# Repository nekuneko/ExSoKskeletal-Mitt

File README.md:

# ExSoKskeletal Mitt
Robotic Hand for ICTUS patients based on SoK (System on Keyring) boards.

Usign Autodesk EAGLE 9.5.2

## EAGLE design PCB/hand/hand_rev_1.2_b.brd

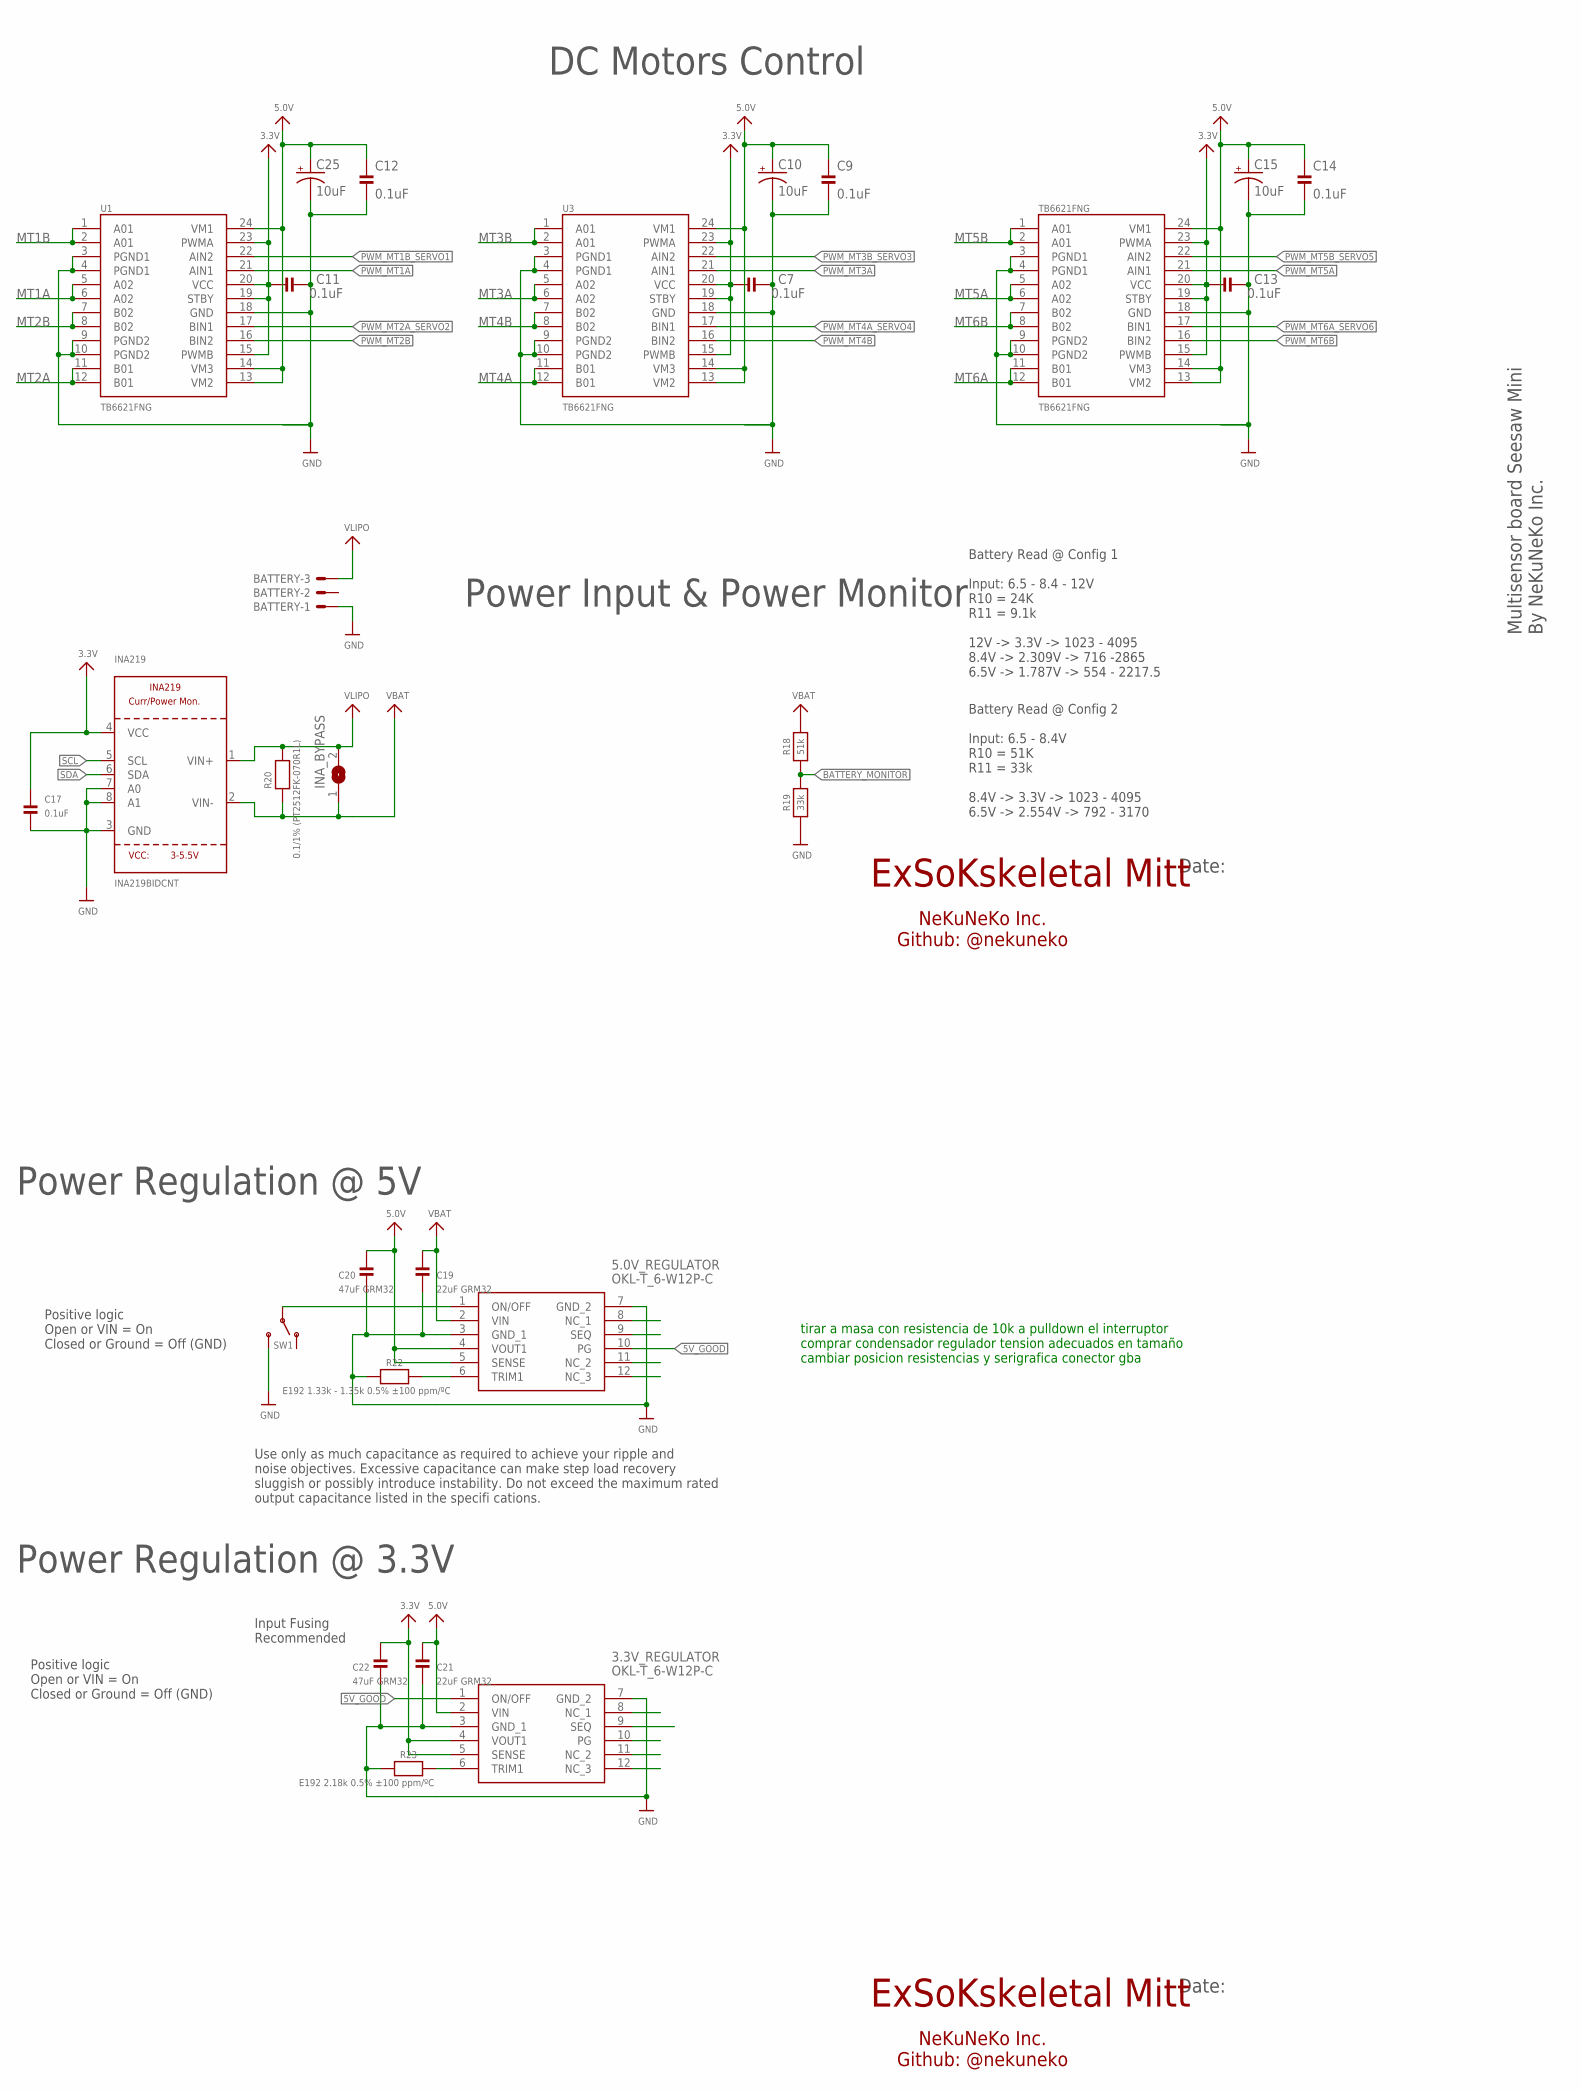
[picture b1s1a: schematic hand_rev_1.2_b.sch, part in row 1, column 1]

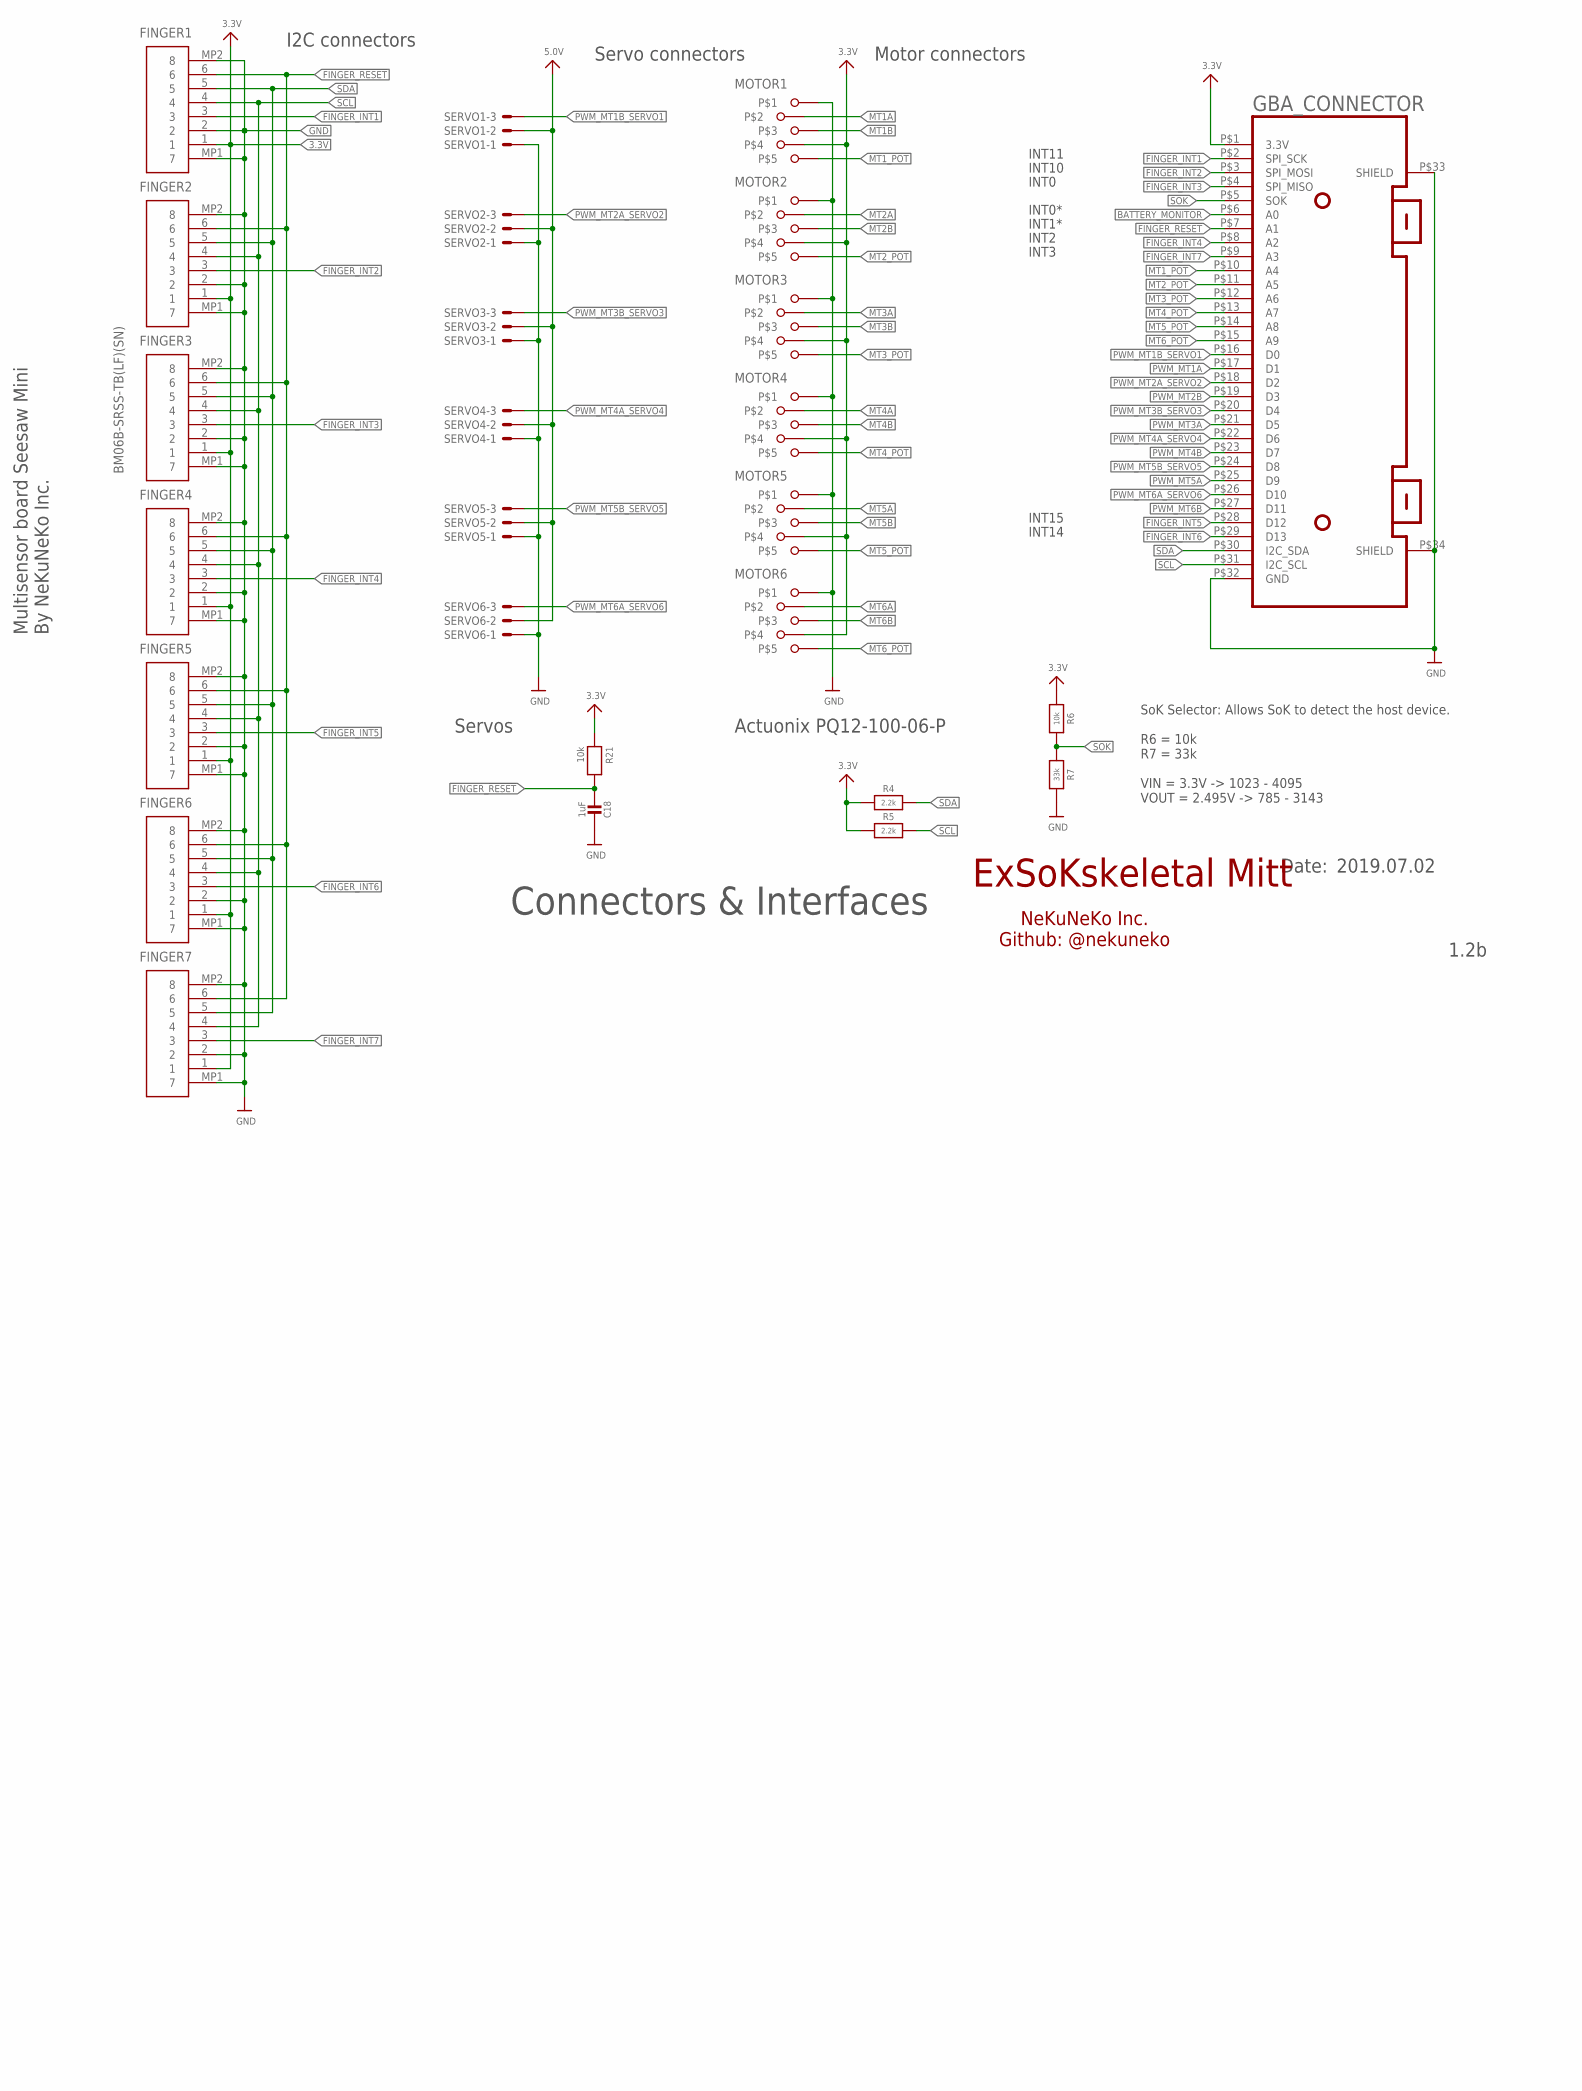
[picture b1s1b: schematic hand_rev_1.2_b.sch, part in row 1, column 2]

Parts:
3.3V_REGULATOR, 5.0V_REGULATOR: OKL-T_6-W12P-C; OKL-T3-W12
BATTERY: JST-XH-03-PIN-LONG-PAD; JST-XH-03-PACKAGE-LONG-PAD
C7, C9, C11, C12, C13, C14, C17: 0.1uF; _0603
C10, C15, C25: 10uF; 0603-POLAR; MPN F981A106MMA
C18: 1uF; MICROBUILDER__0603
C19, C21: 22uF GRM32; 1206
C20, C22: 47uF GRM32; 1206
FINGER1, FINGER2, FINGER3, FINGER4, FINGER5, FINGER6, FINGER7: BM06B-SRSS-TB(LF)(SN); BM06BSRSSTBLFSN
GBA_CONNECTOR: GBA_CARTRIDGEGBA_CARTRIDGE2; GBA_CARTRIDGE2
INA219: INA219BIDCNT; SOT23-8
INA_BYPASS: SOLDERJUMPERREFLOW_NOPASTE; SOLDERJUMPER_REFLOW_NOPASTE
MOTOR1, MOTOR2, MOTOR3, MOTOR4, MOTOR5, MOTOR6: Actuonix PQ12-100-06-P; 5PIN
R4, R5: 2.2k; _0603
R6, R21: 10k; _0603
R7, R19: 33k; _0603
R18: 51k; _0603
R20: 0.1/1% (PT2512FK-070R1L); 2512
R22: E192 1.33k - 1.35k 0.5% ±100 ppm/ºC; _0603
R23: E192 2.18k 0.5% ±100 ppm/ºC; _0603
SERVO1, SERVO2, SERVO3, SERVO4, SERVO5, SERVO6: JST-XH-03-PIN-LONG-PAD; JST-XH-03-PACKAGE-LONG-PAD
SW1: SWITCH_SPDT; SPDT_SMT_SSSS811101
TB6621FNG: TB6621FNG; SSOP24
U1, U3: TB6621FNG; SSOP24

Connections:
3.3V: 3.3V_REGULATOR.4 (VOUT1), 3.3V_REGULATOR.5 (SENSE), C7.1, C11.1, C13.1, C17.2, C22.1, FINGER1.1, FINGER2.1, FINGER3.1, FINGER4.1, FINGER5.1, FINGER6.1, FINGER7.1, GBA_CONNECTOR.P$1 (3.3V), INA219.4 (VCC), MOTOR1.4, MOTOR2.4, MOTOR3.4, MOTOR4.4, MOTOR5.4, MOTOR6.4, R4.1, R5.1, R6.1, R21.1, TB6621FNG.15 (PWMB), TB6621FNG.19 (STBY), TB6621FNG.20 (VCC), TB6621FNG.23 (PWMA), U1.15 (PWMB), U1.19 (STBY), U1.20 (VCC), U1.23 (PWMA), U3.15 (PWMB), U3.19 (STBY), U3.20 (VCC), U3.23 (PWMA)
5.0V: 3.3V_REGULATOR.2 (VIN), 5.0V_REGULATOR.4 (VOUT1), 5.0V_REGULATOR.5 (SENSE), C9.2, C10.+, C12.2, C14.2, C15.+, C20.1, C21.1, C25.+, SERVO1.2, SERVO2.2, SERVO3.2, SERVO4.2, SERVO5.2, SERVO6.2, TB6621FNG.13 (VM2), TB6621FNG.14 (VM3), TB6621FNG.24 (VM1), U1.13 (VM2), U1.14 (VM3), U1.24 (VM1), U3.13 (VM2), U3.14 (VM3), U3.24 (VM1)
5V_GOOD: 3.3V_REGULATOR.1 (ON/OFF), 5.0V_REGULATOR.10 (PG)
BATTERY_MONITOR: GBA_CONNECTOR.P$6 (A0), R18.1, R19.2
FINGER_!RESET: C18.2, FINGER1.6, FINGER2.6, FINGER3.6, FINGER4.6, FINGER5.6, FINGER6.6, FINGER7.6, GBA_CONNECTOR.P$7 (A1), R21.2
FINGER_INT1: FINGER1.3, GBA_CONNECTOR.P$2 (SPI_SCK)
FINGER_INT2: FINGER2.3, GBA_CONNECTOR.P$3 (SPI_MOSI)
FINGER_INT3: FINGER3.3, GBA_CONNECTOR.P$4 (SPI_MISO)
FINGER_INT4: FINGER4.3, GBA_CONNECTOR.P$8 (A2)
FINGER_INT5: FINGER5.3, GBA_CONNECTOR.P$28 (D12)
FINGER_INT6: FINGER6.3, GBA_CONNECTOR.P$29 (D13)
FINGER_INT7: FINGER7.3, GBA_CONNECTOR.P$9 (A3)
GND: 3.3V_REGULATOR.3 (GND_1), 3.3V_REGULATOR.7 (GND_2), 5.0V_REGULATOR.3 (GND_1), 5.0V_REGULATOR.7 (GND_2), BATTERY.1, C7.2, C9.1, C10.-, C11.2, C12.1, C13.2, C14.1, C15.-, C17.1, C18.1, C19.2, C20.2, C21.2, C22.2, C25.-, FINGER1.2, FINGER1.MP1 (7), FINGER1.MP2 (8), FINGER2.2, FINGER2.MP1 (7), FINGER2.MP2 (8), FINGER3.2, FINGER3.MP1 (7), FINGER3.MP2 (8), FINGER4.2, FINGER4.MP1 (7), FINGER4.MP2 (8), FINGER5.2, FINGER5.MP1 (7), FINGER5.MP2 (8), FINGER6.2, FINGER6.MP1 (7), FINGER6.MP2 (8), FINGER7.2, FINGER7.MP1 (7), FINGER7.MP2 (8), GBA_CONNECTOR.P$32 (GND), GBA_CONNECTOR.P$33 (SHIELD), GBA_CONNECTOR.P$34 (SHIELD), INA219.3 (GND), INA219.7 (A0), INA219.8 (A1), MOTOR1.1, MOTOR2.1, MOTOR3.1, MOTOR4.1, MOTOR5.1, MOTOR6.1, R7.2, R19.1, R22.2, R23.2, SERVO1.1, SERVO2.1, SERVO3.1, SERVO4.1, SERVO5.1, SERVO6.1, SW1.C (S), TB6621FNG.3 (PGND1), TB6621FNG.4 (PGND1), TB6621FNG.9 (PGND2), TB6621FNG.10 (PGND2), TB6621FNG.18 (GND), U1.3 (PGND1), U1.4 (PGND1), U1.9 (PGND2), U1.10 (PGND2), U1.18 (GND), U3.3 (PGND1), U3.4 (PGND1), U3.9 (PGND2), U3.10 (PGND2), U3.18 (GND)
MT1A: MOTOR1.2, U1.5 (A02), U1.6 (A02)
MT1B: MOTOR1.3, U1.1 (A01), U1.2 (A01)
MT1_POT: GBA_CONNECTOR.P$10 (A4), MOTOR1.5
MT2A: MOTOR2.2, U1.11 (B01), U1.12 (B01)
MT2B: MOTOR2.3, U1.7 (B02), U1.8 (B02)
MT2_POT: GBA_CONNECTOR.P$11 (A5), MOTOR2.5
MT3A: MOTOR3.2, U3.5 (A02), U3.6 (A02)
MT3B: MOTOR3.3, U3.1 (A01), U3.2 (A01)
MT3_POT: GBA_CONNECTOR.P$12 (A6), MOTOR3.5
MT4A: MOTOR4.2, U3.11 (B01), U3.12 (B01)
MT4B: MOTOR4.3, U3.7 (B02), U3.8 (B02)
MT4_POT: GBA_CONNECTOR.P$13 (A7), MOTOR4.5
MT5A: MOTOR5.2, TB6621FNG.5 (A02), TB6621FNG.6 (A02)
MT5B: MOTOR5.3, TB6621FNG.1 (A01), TB6621FNG.2 (A01)
MT5_POT: GBA_CONNECTOR.P$14 (A8), MOTOR5.5
MT6A: MOTOR6.2, TB6621FNG.11 (B01), TB6621FNG.12 (B01)
MT6B: MOTOR6.3, TB6621FNG.7 (B02), TB6621FNG.8 (B02)
MT6_POT: GBA_CONNECTOR.P$15 (A9), MOTOR6.5
unnamed: 5.0V_REGULATOR.6 (TRIM1), R22.1
unnamed: 3.3V_REGULATOR.6 (TRIM1), R23.1
PWM_MT1A: GBA_CONNECTOR.P$17 (D1), U1.21 (AIN1)
PWM_MT1B_SERVO1: GBA_CONNECTOR.P$16 (D0), SERVO1.3, U1.22 (AIN2)
PWM_MT2A_SERVO2: GBA_CONNECTOR.P$18 (D2), SERVO2.3, U1.17 (BIN1)
PWM_MT2B: GBA_CONNECTOR.P$19 (D3), U1.16 (BIN2)
PWM_MT3A: GBA_CONNECTOR.P$21 (D5), U3.21 (AIN1)
PWM_MT3B_SERVO3: GBA_CONNECTOR.P$20 (D4), SERVO3.3, U3.22 (AIN2)
PWM_MT4A_SERVO4: GBA_CONNECTOR.P$22 (D6), SERVO4.3, U3.17 (BIN1)
PWM_MT4B: GBA_CONNECTOR.P$23 (D7), U3.16 (BIN2)
PWM_MT5A: GBA_CONNECTOR.P$25 (D9), TB6621FNG.21 (AIN1)
PWM_MT5B_SERVO5: GBA_CONNECTOR.P$24 (D8), SERVO5.3, TB6621FNG.22 (AIN2)
PWM_MT6A_SERVO6: GBA_CONNECTOR.P$26 (D10), SERVO6.3, TB6621FNG.17 (BIN1)
PWM_MT6B: GBA_CONNECTOR.P$27 (D11), TB6621FNG.16 (BIN2)
REG_5V_ON: 5.0V_REGULATOR.1 (ON/OFF), SW1.B
SCL: FINGER1.4, FINGER2.4, FINGER3.4, FINGER4.4, FINGER5.4, FINGER6.4, FINGER7.4, GBA_CONNECTOR.P$31 (I2C_SCL), INA219.5 (SCL), R5.2
SDA: FINGER1.5, FINGER2.5, FINGER3.5, FINGER4.5, FINGER5.5, FINGER6.5, FINGER7.5, GBA_CONNECTOR.P$30 (I2C_SDA), INA219.6 (SDA), R4.2
SOK: GBA_CONNECTOR.P$5 (SOK), R6.2, R7.1
VBAT: 5.0V_REGULATOR.2 (VIN), C19.1, INA219.2 (VIN-), INA_BYPASS.1, R18.2, R20.1
VLIPO: BATTERY.3, INA219.1 (VIN+), INA_BYPASS.2, R20.2

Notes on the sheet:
ExSoKskeletal Mitt
INT11
INT10
INT0
INT0*
INT1*
INT2
INT3
INT14
INT15
Battery Read @ Config 2 Input: 6.5 - 8.4V R10 = 51K R11 = 33k 8.4V -> 3.3V -> 1023 - 4095 6.5V -> 2.554V -> 792 - 3170
Power Input & Power Monitor
Power Regulation @ 5V
Power Regulation @ 3.3V
DC Motors Control
Connectors & Interfaces
NeKuNeKo Inc. Github: @nekuneko
Date:
SoK Selector: Allows SoK to detect the host device. R6 = 10k R7 = 33k VIN = 3.3V -> 1023 - 4095 VOUT = 2.495V -> 785 - 3143
I2C connectors
Servo connectors
Motor connectors
Actuonix PQ12-100-06-P
Multisensor board Seesaw Mini By NeKuNeKo Inc.
Servos
Battery Read @ Config 1 Input: 6.5 - 8.4 - 12V R10 = 24K R11 = 9.1k 12V -> 3.3V -> 1023 - 4095 8.4V -> 2.309V -> 716 -2865 6.5V -> 1.787V -> 554 - 2217.5
Input Fusing Recommended
Positive logic Open or VIN = On Closed or Ground = Off (GND)
Use only as much capacitance as required to achieve your ripple and noise objectives. Excessive capacitance can make step load recovery sluggish or possibly introduce instability. Do not exceed the maximum rated output capacitance listed in the specifi cations.
tirar a masa con resistencia de 10k a pulldown el interruptor comprar condensador regulador tension adecuados en tamaño cambiar posicion resistencias y serigrafica conector gba

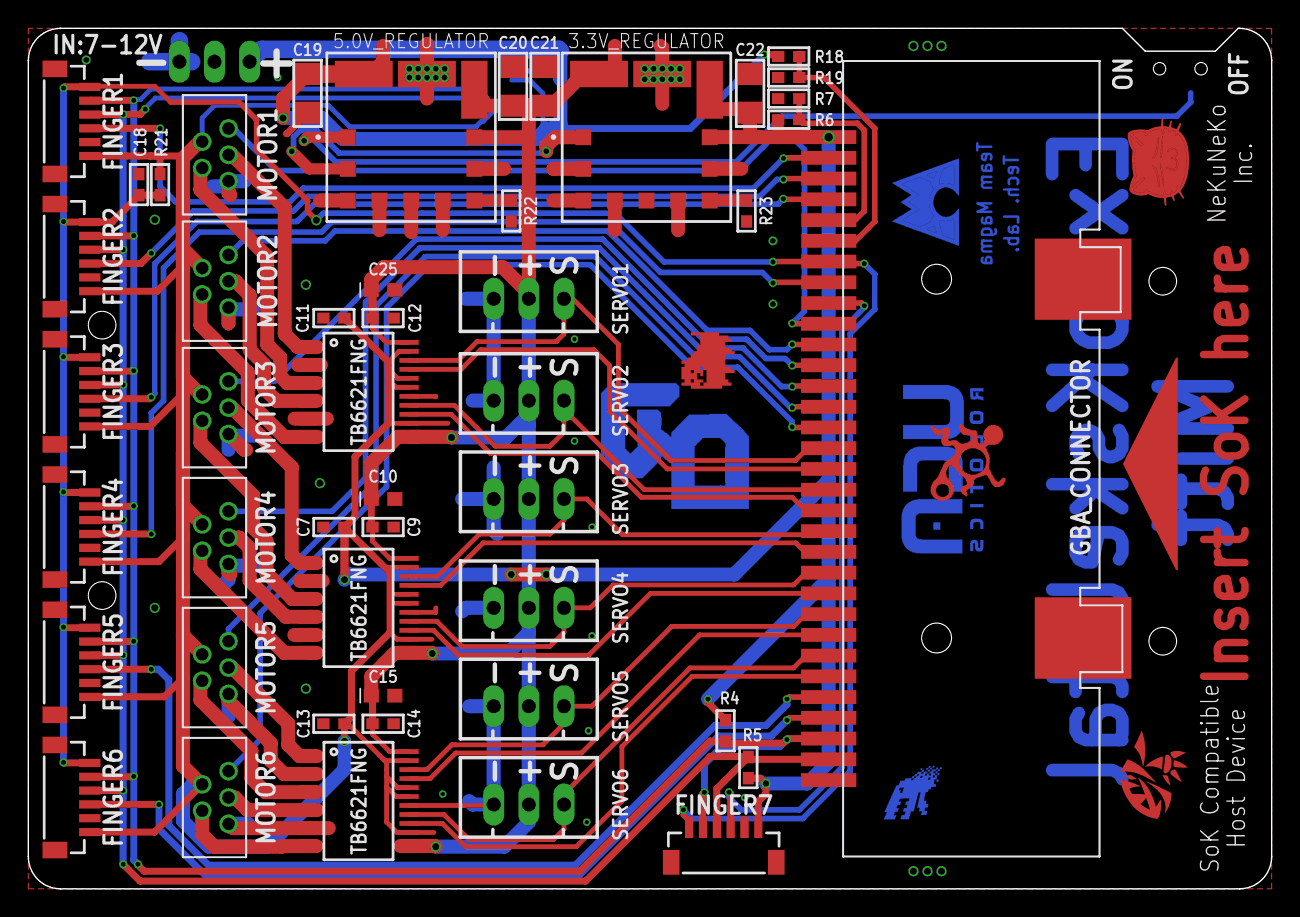
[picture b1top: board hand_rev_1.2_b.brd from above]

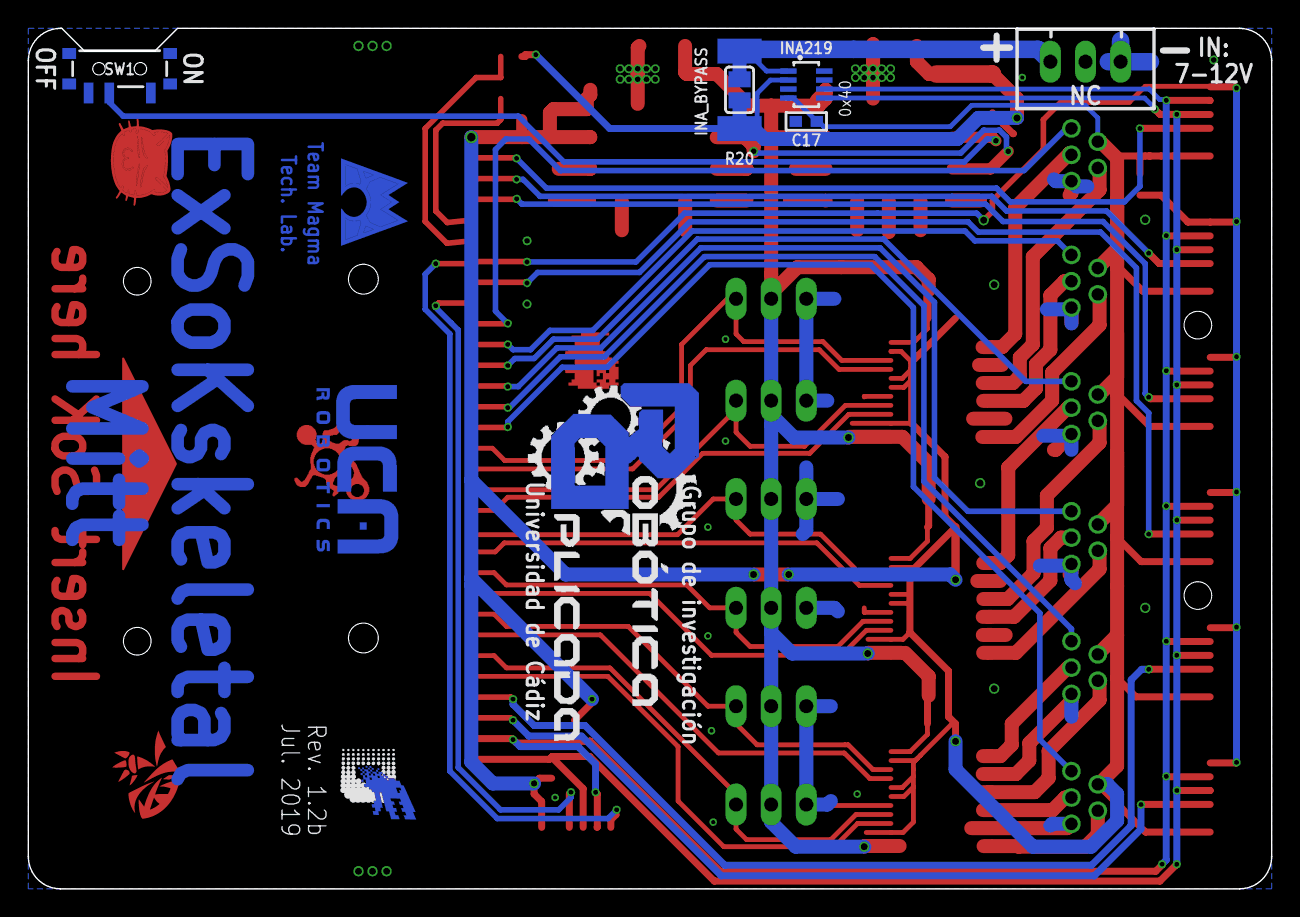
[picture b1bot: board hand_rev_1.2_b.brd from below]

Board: 2 copper layers, 89.9 x 62.2 mm, 63 parts (10 on the bottom side), 51 nets.

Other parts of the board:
U$6: NEKO_6_5_BORDE_TSTOP
U$7: SOK_FINISH
U$8: DOG_FINISH
U$9: MAGMA
U$14: UCAROBOTICS
U$48: GIRA_2_DRAWN_14
U$50: TRIANGLE
U$51: DIGIMON
U$52: BUGS_6

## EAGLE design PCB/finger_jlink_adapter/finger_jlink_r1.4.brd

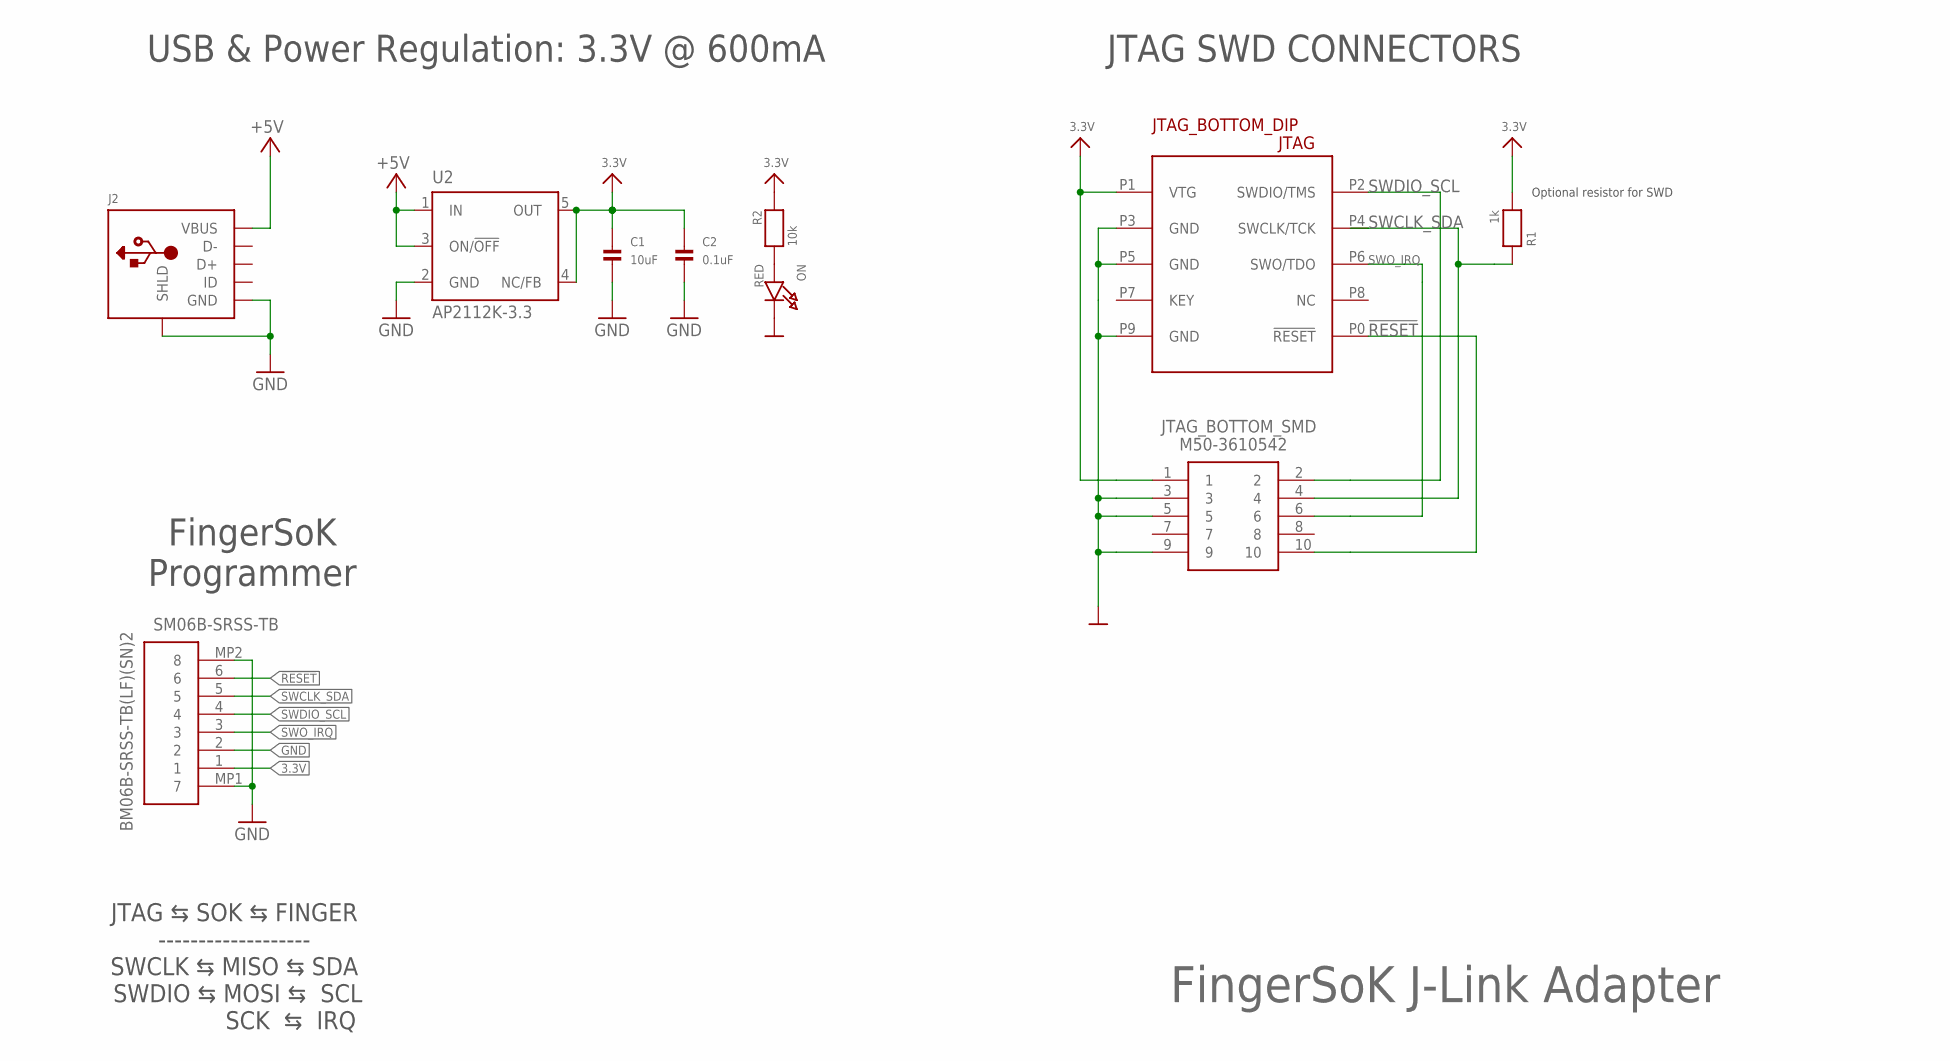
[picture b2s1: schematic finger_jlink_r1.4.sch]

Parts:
C1: 10uF; _0402
C2: 0.1uF; _0402
J2: FLAT_MICROUSB_ALIEXPRESS_TYPE_4; USB_TYPE_4_105164-0001
JTAG_BOTTOM_DIP: JTAGICE3-CONNECTOR50MIL-THT; JTAGICE3-50MIL
JTAG_BOTTOM_SMD: M50-3610542; M503610542
ON: RED; CHIPLED_0603
R1: 1k; _0402
R2: 10k; _0402
SM06B-SRSS-TB: BM06B-SRSS-TB(LF)(SN)2; BM06B-SRSS-TB(LF)(SN)_2
U2: AP2112K-3.3; SOT23-DBV

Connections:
3.3V: C1.1, C2.1, JTAG_BOTTOM_DIP.P1 (VTG), JTAG_BOTTOM_SMD.1, R1.2, R2.2, SM06B-SRSS-TB.1, U2.4 (NC/FB), U2.5 (OUT)
!RESET: JTAG_BOTTOM_DIP.P0 (!RESET), JTAG_BOTTOM_SMD.10, SM06B-SRSS-TB.6
+5V: J2.P$5 (VBUS), U2.1 (IN), U2.3 (ON/!OFF)
GND: C1.2, C2.2, J2.P$1 (GND), J2.P$8 (SHLD), J2.P$9 (SHLD), JTAG_BOTTOM_DIP.P3 (GND), JTAG_BOTTOM_DIP.P5 (GND), JTAG_BOTTOM_DIP.P9 (GND), JTAG_BOTTOM_SMD.3, JTAG_BOTTOM_SMD.5, JTAG_BOTTOM_SMD.9, ON.C, SM06B-SRSS-TB.2, SM06B-SRSS-TB.MP1 (7), SM06B-SRSS-TB.MP2 (8), U2.2 (GND)
unnamed: ON.A, R2.1
SWCLK_SDA: JTAG_BOTTOM_DIP.P4 (SWCLK/TCK), JTAG_BOTTOM_SMD.4, R1.1, SM06B-SRSS-TB.5
SWDIO_SCL: JTAG_BOTTOM_DIP.P2 (SWDIO/TMS), JTAG_BOTTOM_SMD.2, SM06B-SRSS-TB.4
SWO_IRQ: JTAG_BOTTOM_DIP.P6 (SWO/TDO), JTAG_BOTTOM_SMD.6, SM06B-SRSS-TB.3

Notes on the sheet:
Optional resistor for SWD
FingerSoK J-Link Adapter
JTAG ⇆ SOK ⇆ FINGER ------------------- SWCLK ⇆ MISO ⇆ SDA SWDIO ⇆ MOSI ⇆ SCL SCK ⇆ IRQ
FingerSoK Programmer
USB & Power Regulation: 3.3V @ 600mA
JTAG SWD CONNECTORS

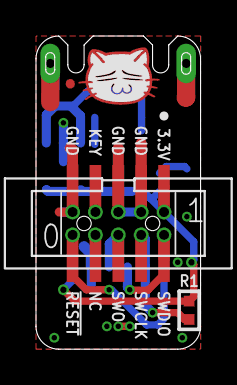
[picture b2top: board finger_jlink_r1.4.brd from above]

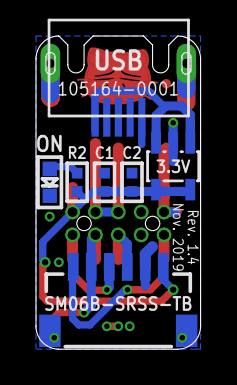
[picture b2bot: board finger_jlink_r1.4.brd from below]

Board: 2 copper layers, 9.1 x 17.4 mm, 12 parts (8 on the bottom side), 8 nets.

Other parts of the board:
U$4: NEKO_5_3_WHITEFACE
U$5: USB_TYPE_4_DIM

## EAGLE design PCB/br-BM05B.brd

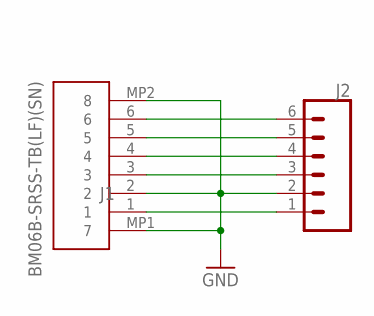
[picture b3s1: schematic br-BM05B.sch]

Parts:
J1: BM06B-SRSS-TB(LF)(SN); BM06BSRSSTBLFSN
J2: CONN_06NO_SILK_FEMALE_PTH; 1X06_NO_SILK

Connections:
GND: J1.2, J1.MP1 (7), J1.MP2 (8), J2.2
unnamed: J1.1, J2.1
unnamed: J1.3, J2.3
unnamed: J1.4, J2.4
unnamed: J1.5, J2.5
unnamed: J1.6, J2.6

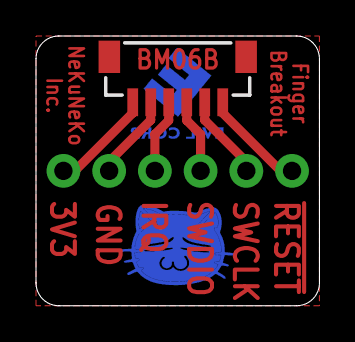
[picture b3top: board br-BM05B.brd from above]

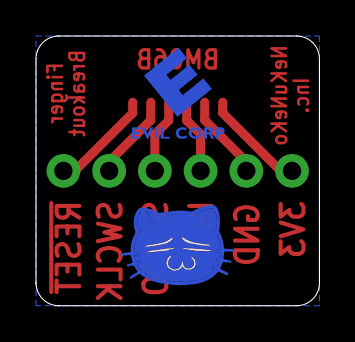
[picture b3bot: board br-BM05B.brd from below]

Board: 2 copper layers, 15.7 x 15.0 mm, 4 parts (2 on the bottom side), 6 nets.

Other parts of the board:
U$1: NEKO_6_5_BORDE_SILK
U$2: ECORP_TSTOP_6

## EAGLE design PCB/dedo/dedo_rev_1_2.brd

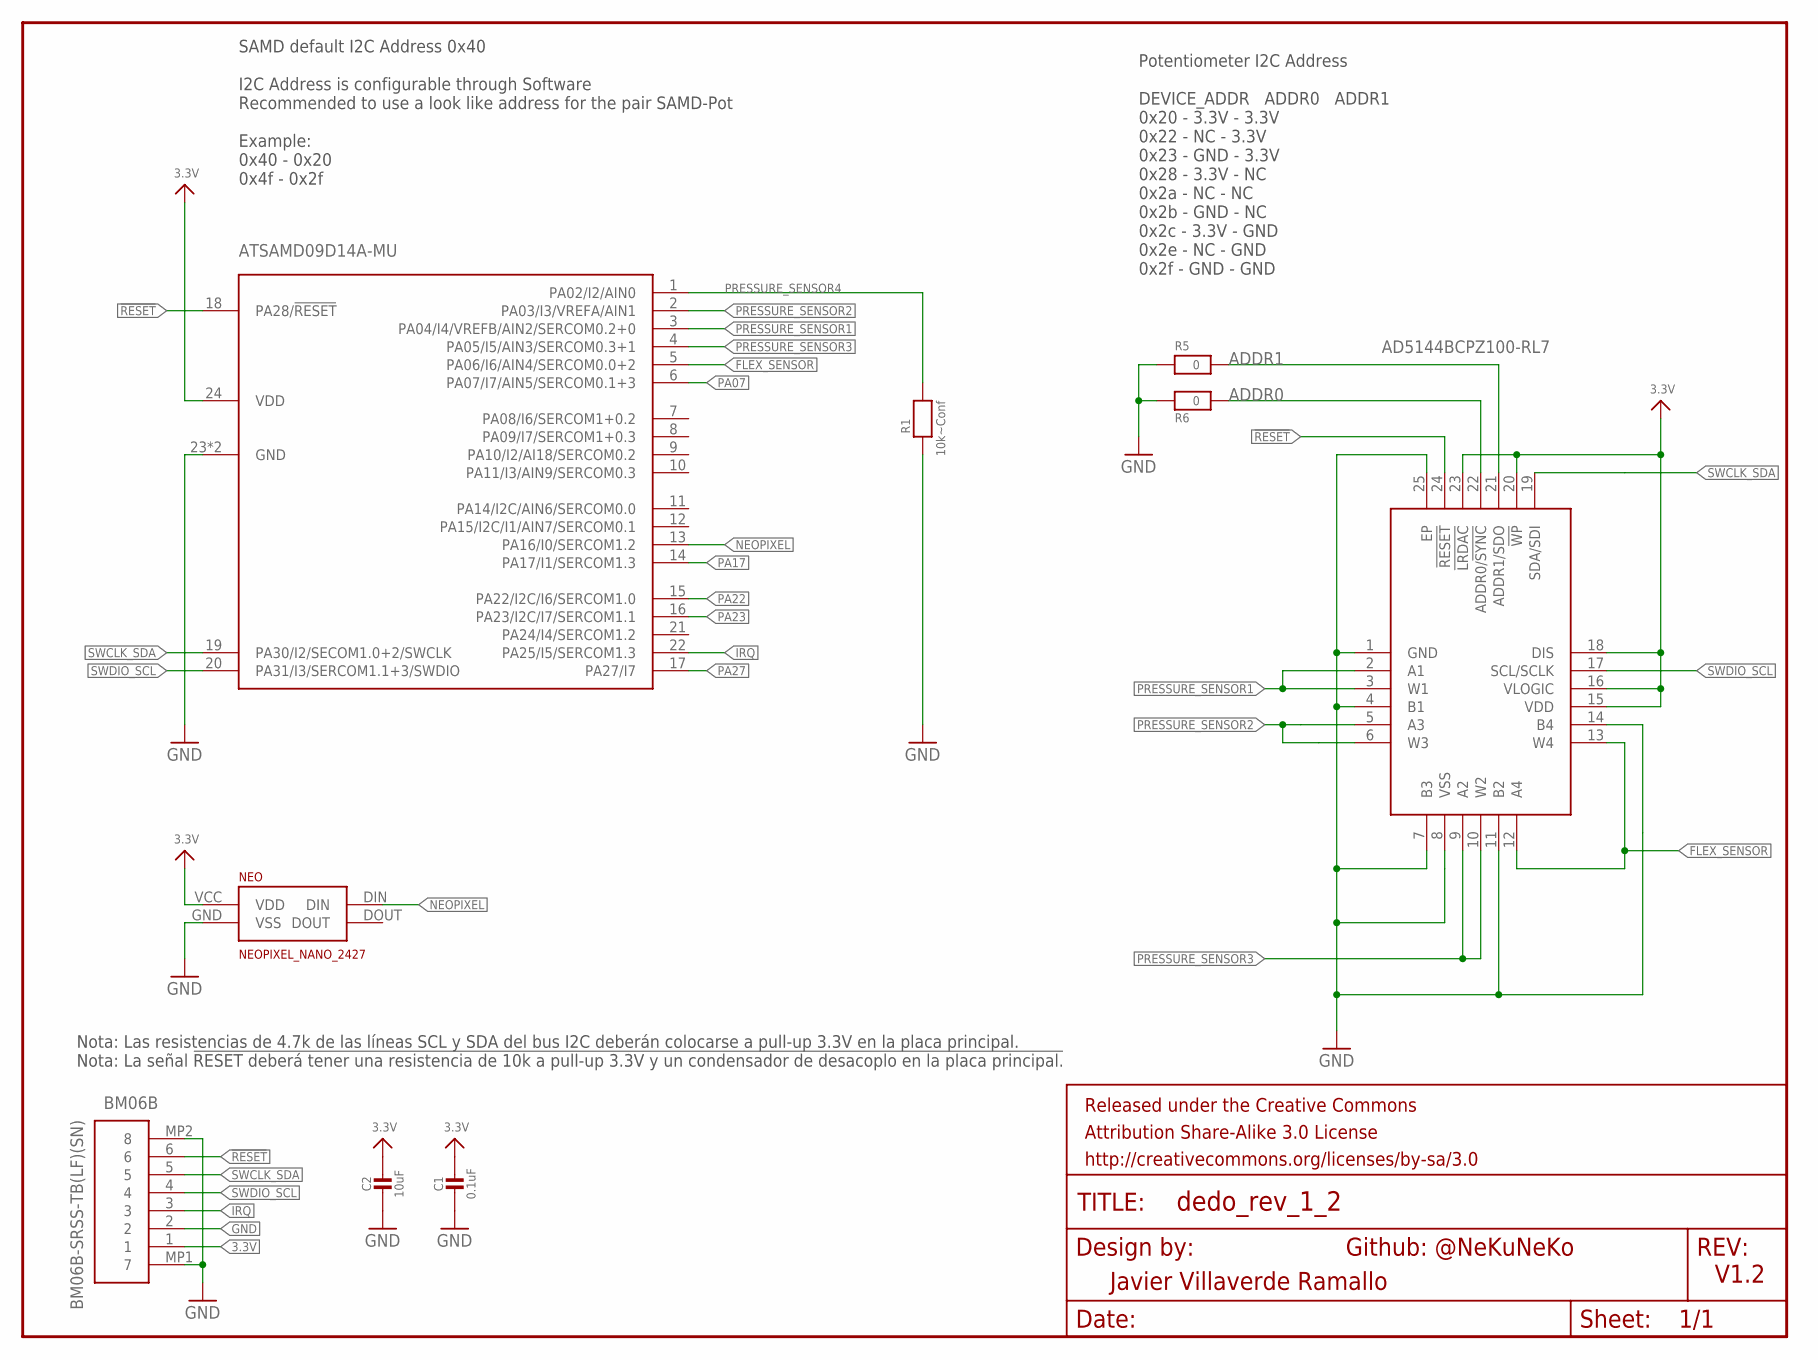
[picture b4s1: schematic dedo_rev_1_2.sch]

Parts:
AD5144BCPZ100: AD5144BCPZ100-RL7; QFN50P400X400X80-25N
BM06B: BM06B-SRSS-TB(LF)(SN); BM06BSRSSTBLFSN
C1: 0.1uF; 0402
C2: 10uF; 0402
FRAME1, FRAME2: FRAME-LETTER; CREATIVE_COMMONS
NEO: NEOPIXEL_NANO_2427; SK6805-2427
R1: 10k~Conf; _0402
R5, R6: 0; _0402
SAMD09: ATSAMD09D14A-MU; QFN24_4MM

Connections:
3.3V: AD5144BCPZ100.15 (VDD), AD5144BCPZ100.16 (VLOGIC), AD5144BCPZ100.18 (DIS), AD5144BCPZ100.20 (!WP), AD5144BCPZ100.23 (!LRDAC), BM06B.1, C1.1, C2.1, NEO.VCC (VDD), SAMD09.24 (VDD)
!RESET: AD5144BCPZ100.24 (!RESET), BM06B.6, SAMD09.18 (PA28/!RESET)
ADDR0: AD5144BCPZ100.22 (ADDR0/!SYNC), R6.2
ADDR1: AD5144BCPZ100.21 (ADDR1/SDO), R5.2
FLEX_SENSOR: AD5144BCPZ100.12 (A4), AD5144BCPZ100.13 (W4), SAMD09.5 (PA06/I6/AIN4/SERCOM0.0+2)
GND: AD5144BCPZ100.1 (GND), AD5144BCPZ100.4 (B1), AD5144BCPZ100.7 (B3), AD5144BCPZ100.8 (VSS), AD5144BCPZ100.11 (B2), AD5144BCPZ100.14 (B4), AD5144BCPZ100.25 (EP), BM06B.2, BM06B.MP1 (7), BM06B.MP2 (8), C1.2, C2.2, NEO.GND (VSS), R1.2, R5.1, R6.1, SAMD09.23 (GND), SAMD09.THERM (GND)
IRQ: BM06B.3, SAMD09.22 (PA25/I5/SERCOM1.3)
NEOPIXEL: NEO.DIN, SAMD09.13 (PA16/I0/SERCOM1.2)
PA07: SAMD09.6 (PA07/I7/AIN5/SERCOM0.1+3)
PA17: SAMD09.14 (PA17/I1/SERCOM1.3)
PA22: SAMD09.15 (PA22/I2C/I6/SERCOM1.0)
PA23: SAMD09.16 (PA23/I2C/I7/SERCOM1.1)
PA27: SAMD09.17 (PA27/I7)
PRESSURE_SENSOR1: AD5144BCPZ100.2 (A1), AD5144BCPZ100.3 (W1), SAMD09.3 (PA04/I4/VREFB/AIN2/SERCOM0.2+0)
PRESSURE_SENSOR2: AD5144BCPZ100.5 (A3), AD5144BCPZ100.6 (W3), SAMD09.2 (PA03/I3/VREFA/AIN1)
PRESSURE_SENSOR3: AD5144BCPZ100.9 (A2), AD5144BCPZ100.10 (W2), SAMD09.4 (PA05/I5/AIN3/SERCOM0.3+1)
PRESSURE_SENSOR4: R1.1, SAMD09.1 (PA02/I2/AIN0)
SWCLK_SDA: AD5144BCPZ100.19 (SDA/SDI), BM06B.5, SAMD09.19 (PA30/I2/SECOM1.0+2/SWCLK)
SWDIO_SCL: AD5144BCPZ100.17 (SCL/SCLK), BM06B.4, SAMD09.20 (PA31/I3/SERCOM1.1+3/SWDIO)

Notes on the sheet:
Nota: Las resistencias de 4.7k de las líneas SCL y SDA del bus I2C deberán colocarse a pull-up 3.3V en la placa principal. Nota: La señal !RESET deberá tener una resistencia de 10k a pull-up 3.3V y un condensador de desacoplo en la placa principal.
Github: @NeKuNeKo
V1.2
Javier Villaverde Ramallo
Potentiometer I2C Address DEVICE_ADDR ADDR0 ADDR1 0x20 - 3.3V - 3.3V 0x22 - NC - 3.3V 0x23 - GND - 3.3V 0x28 - 3.3V - NC 0x2a - NC - NC 0x2b - GND - NC 0x2c - 3.3V - GND 0x2e - NC - GND 0x2f - GND - GND
SAMD default I2C Address 0x40 I2C Address is configurable through Software Recommended to use a look like address for the pair SAMD-Pot Example: 0x40 - 0x20 0x4f - 0x2f

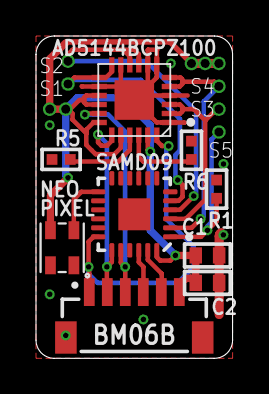
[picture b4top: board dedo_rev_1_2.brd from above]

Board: 2 copper layers, 10.9 x 17.9 mm, 12 parts (1 on the bottom side), 14 nets.

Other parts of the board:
U$1: NEKO_DRAWN

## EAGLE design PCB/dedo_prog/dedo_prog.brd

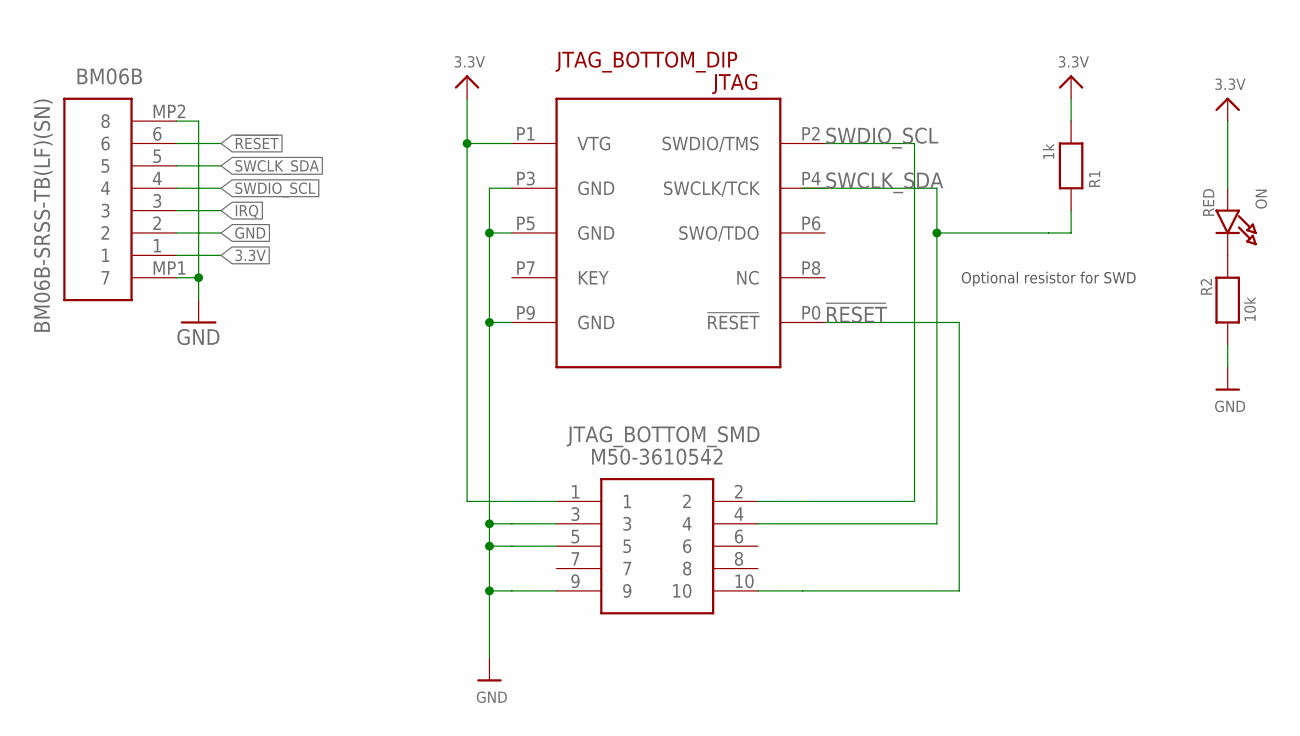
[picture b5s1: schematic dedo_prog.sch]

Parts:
BM06B: BM06B-SRSS-TB(LF)(SN); BM06BSRSSTBLFSN
JTAG_BOTTOM_DIP: JTAGICE3-CONNECTOR50MIL-THT; JTAGICE3-50MIL
JTAG_BOTTOM_SMD: M50-3610542; M503610542
ON: RED; CHIPLED_0603
R1: 1k; _0402@1
R2: 10k; _0402@1

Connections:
3.3V: BM06B.1, JTAG_BOTTOM_DIP.P1 (VTG), JTAG_BOTTOM_SMD.1, ON.A, R1.2
!RESET: BM06B.6, JTAG_BOTTOM_DIP.P0 (!RESET), JTAG_BOTTOM_SMD.10
GND: BM06B.2, BM06B.MP1 (7), BM06B.MP2 (8), JTAG_BOTTOM_DIP.P3 (GND), JTAG_BOTTOM_DIP.P5 (GND), JTAG_BOTTOM_DIP.P9 (GND), JTAG_BOTTOM_SMD.3, JTAG_BOTTOM_SMD.5, JTAG_BOTTOM_SMD.9, R2.1
IRQ: BM06B.3
unnamed: ON.C, R2.2
SWCLK_SDA: BM06B.5, JTAG_BOTTOM_DIP.P4 (SWCLK/TCK), JTAG_BOTTOM_SMD.4, R1.1
SWDIO_SCL: BM06B.4, JTAG_BOTTOM_DIP.P2 (SWDIO/TMS), JTAG_BOTTOM_SMD.2

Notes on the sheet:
Optional resistor for SWD

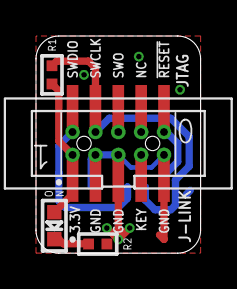
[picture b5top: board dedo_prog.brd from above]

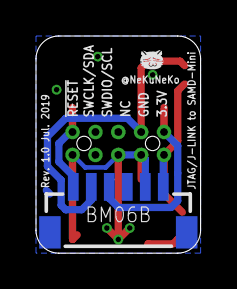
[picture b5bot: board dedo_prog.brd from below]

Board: 2 copper layers, 9.1 x 12.1 mm, 7 parts (2 on the bottom side), 6 nets.

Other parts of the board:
U$1: NEKO_2_1_TSTOP_TPLACE

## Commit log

2019-07-13 Documentation
2019-08-30 Cambio de nombres y ubicación
2019-08-30 Breakout del conector BM05B
2019-08-30 Mini Programador para Finger SoK
2019-08-30 Mano robótica con regulador de tensión 3.3V 2A TPS
2019-09-24 Updated pinout
2019-10-11 Change name
2019-11-14 Renaming
2019-11-14 Finger Rev 1.3: Resistor R5 is doubled to GND and 3.3V to allow potentiometer select I2C address easily.
2019-11-14 Added changelog
2019-11-14 Rev 1.3: Corrected FingerSoK pinout and added serigraph changes
2019-11-14 Changes in serigraph and now Led ON es below the board, following KittySyringe 1.1 design.
2019-11-20 renaming & realocate files

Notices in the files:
parts and their libraries:
SparkFun-Connectors: Licensing: Creative Commons ShareAlike 4.0 International - https://creativecommons.org/licenses/by-sa/4.0
microbuilder: This work is placed in the public domain, and may be freely used for commercial and non-commercial work with the following conditions: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
